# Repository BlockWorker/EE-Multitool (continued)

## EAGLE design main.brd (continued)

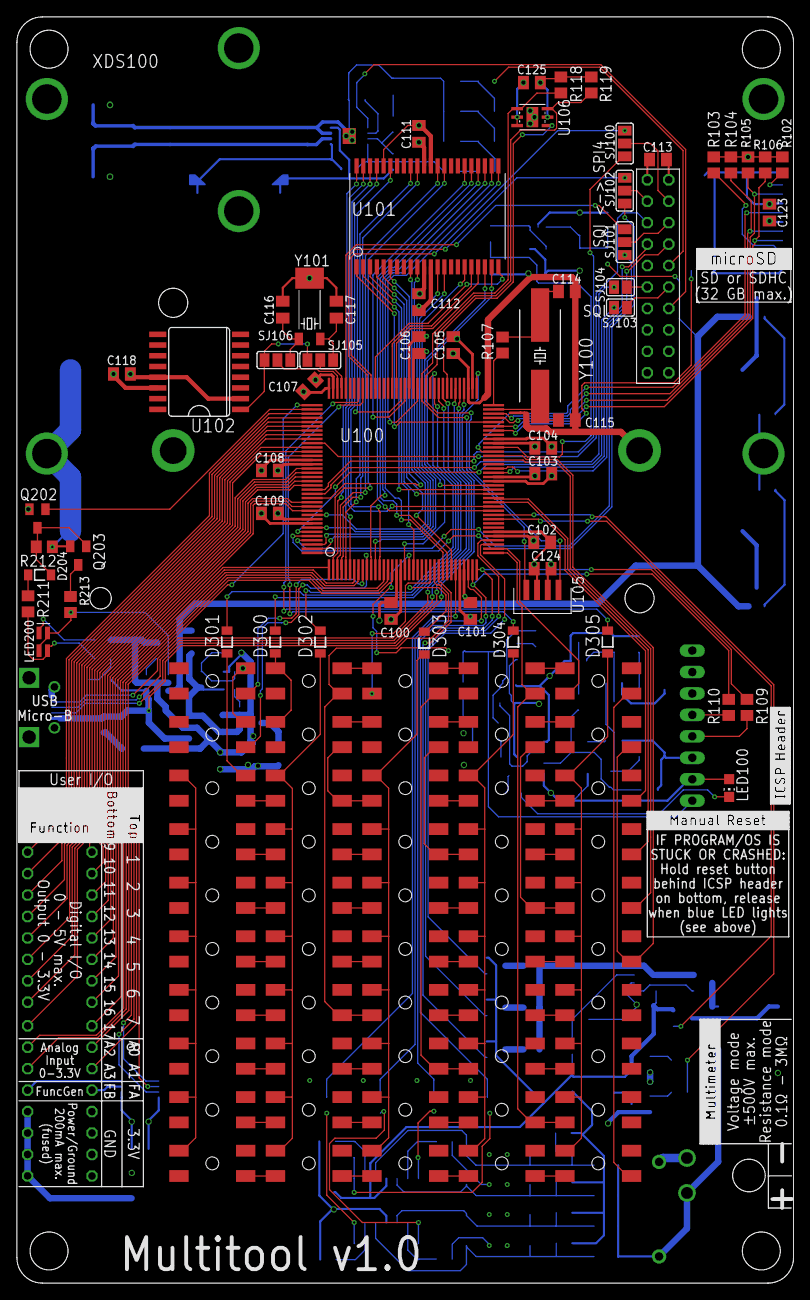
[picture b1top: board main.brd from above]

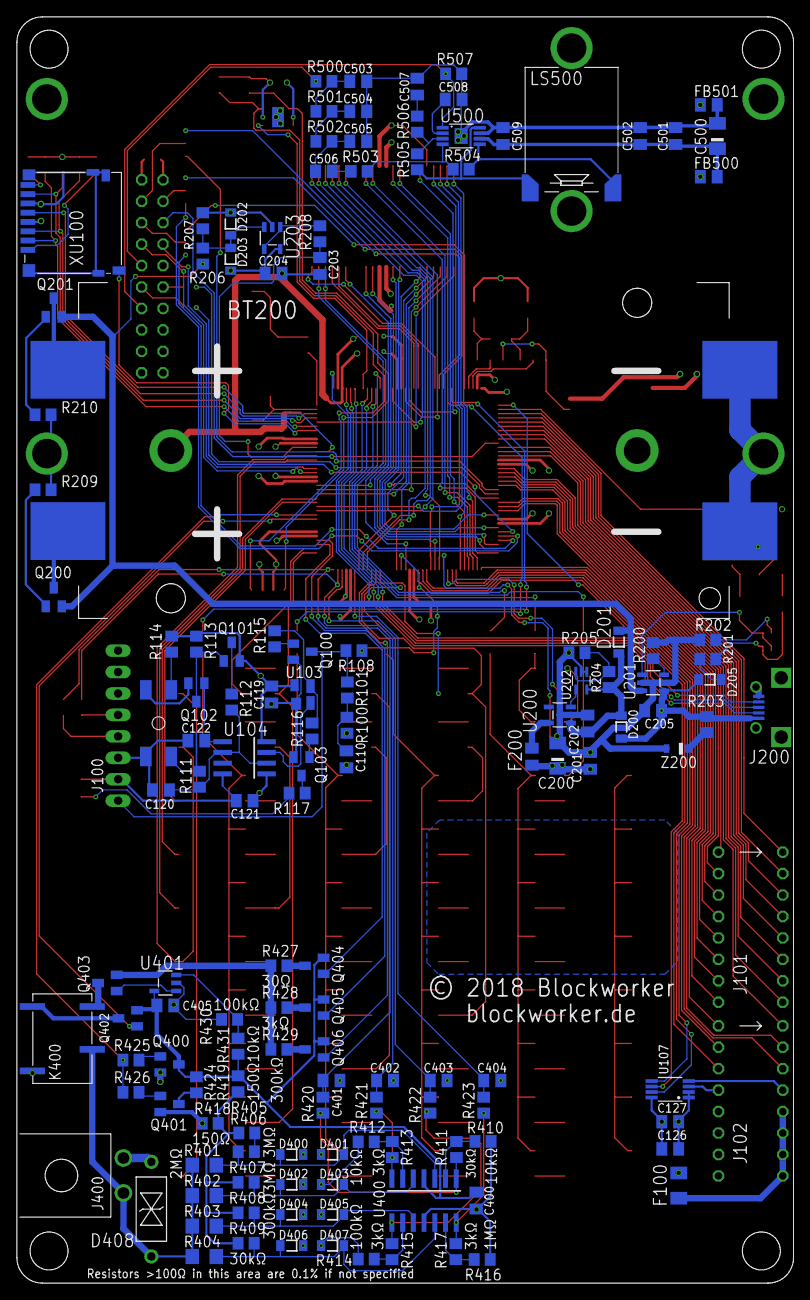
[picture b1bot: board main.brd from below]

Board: 4 copper layers, 92.0 x 150.0 mm, 251 parts (141 on the bottom side), 210 nets.
